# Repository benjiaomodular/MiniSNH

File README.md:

# MiniSNH

An analog sample-and-hold module for Eurorack. It has random gates and trigger outputs that are in-sync with trigger input.

Turning the bias knob to one side makes the probability of the gates firing on one side higher than the other.

# Versions

## v1.0 - Initial Prototype
Does not work!!

- No mounting holes
- Holes for jacks too small
- Swapped negative and postiive power pins of U5 and U6
- Gate in for comparator was wired the wrong way (always high)

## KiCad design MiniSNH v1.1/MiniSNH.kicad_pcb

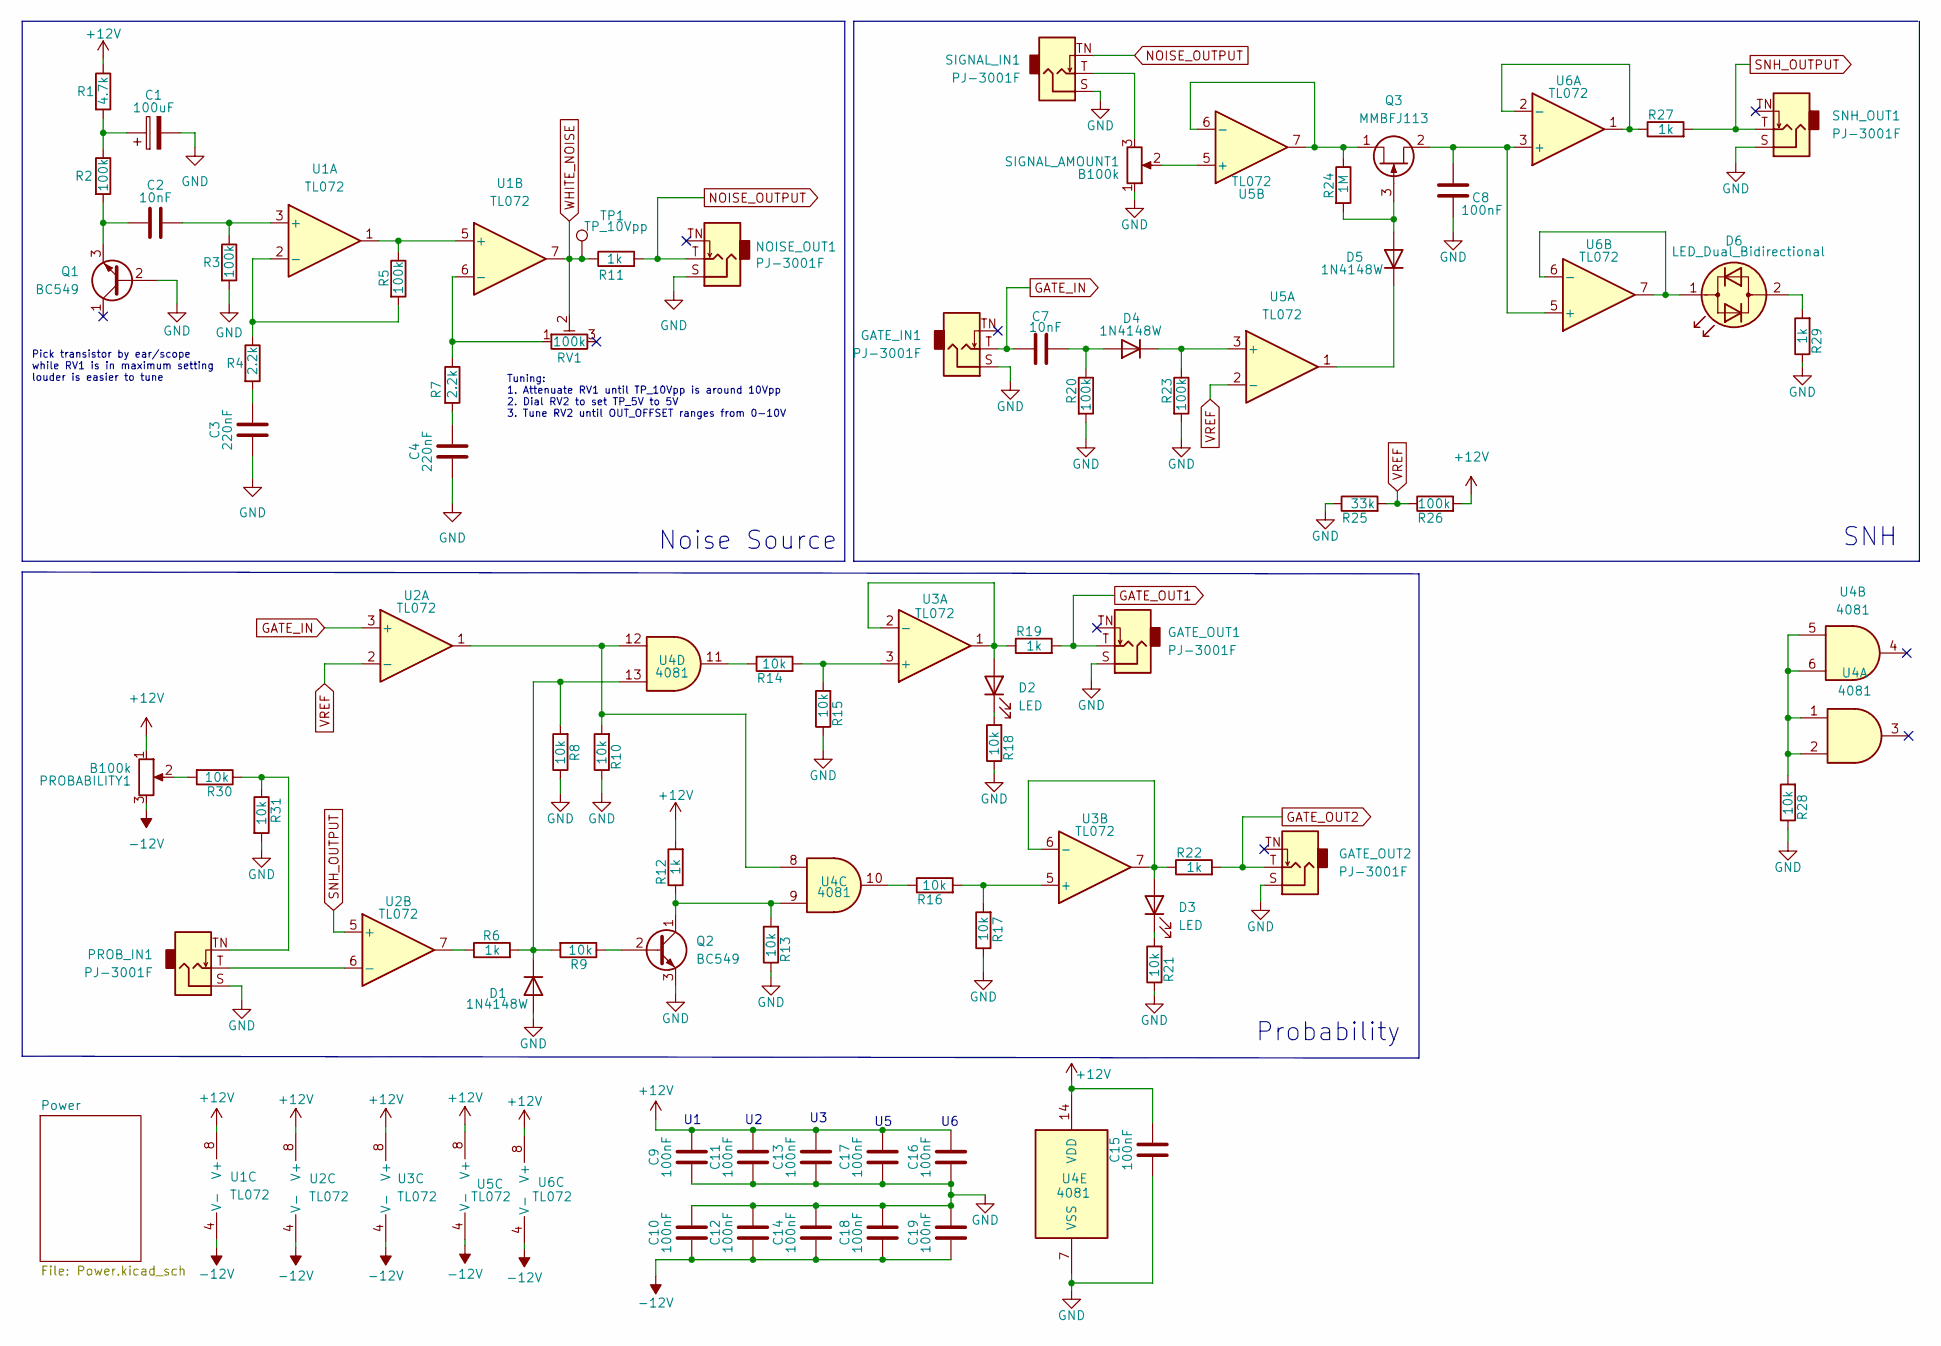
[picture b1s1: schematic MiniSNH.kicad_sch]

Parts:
C1: 100uF; Capacitor_Radial_D5.0mm_P2.5mm; Manufacturers Part Numb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 ESH107M010AC3AA
C2, C7: 10nF; C_0603_1608Metric_Pad1.08x0.95mm_HandSolder; Manufacturers Part Numb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 CC0603JRX7R9BB103
C3, C4: 220nF; C_0603_1608Metric_Pad1.08x0.95mm_HandSolder; Manufacturers Part Numb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 GCM188R71H224KA64D
C8, C9, C10, C11, C12, C13, C14, C15, C16, C17, C18, C19: 100nF; C_0603_1608Metric_Pad1.08x0.95mm_HandSolder; Manufacturers Part Numb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 CC0603JRX7R9BB104
D1, D4, D5: 1N4148W; D_SOD-123; Manufacturers Part Numb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 1N4148WQ-7-F
D2, D3: LED; LED_D3.0mm; Manufacturers Part Numb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 A-261
D6: LED_Dual_Bidirectional; LED_D3.0mm; Manufacturers Part Numb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 3ARG4HWC
GATE_IN1: PJ-3001F; AudioJack_3.5mm; Manufacturers Part Numb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 PJ-3001F
GATE_OUT1, GATE_OUT2: PJ-3001F; AudioJack_3.5mm; Manufacturers Part Numb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 PJ-3001F
NOISE_OUT1: PJ-3001F; AudioJack_3.5mm; Manufacturers Part Numb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 PJ-3001F
PROBABILITY1: B100k; Potentiometer_RV09_NoBracket; Manufacturers Part Numb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 RD901F-40-15R1-B100K
PROB_IN1: PJ-3001F; AudioJack_3.5mm; Manufacturers Part Numb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 PJ-3001F
Q1: BC549; TO-92_Inline_Wide; Manufacturers Part Numb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 BC548BTA
Q2: BC549; TO-92_Inline_Wide; Manufacturers Part Numb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 BC549BTF
Q3: MMBFJ113; SOT-23; Manufacturers Part Numb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 MMBFJ113
R1: 4.7k; R_0603_1608Metric_Pad0.98x0.95mm_HandSolder; Manufacturers Part Numb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 RC0603FR-074K7L
R2, R3, R5, R20, R23, R26: 100k; R_0603_1608Metric_Pad0.98x0.95mm_HandSolder; Manufacturers Part Numb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 RC0603FR-07100KL
R4, R7: 2.2k; R_0603_1608Metric_Pad0.98x0.95mm_HandSolder; Manufacturers Part Numb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 RK73B1JTTD222J
R6, R11, R12, R19, R22, R27, R29: 1k; R_0603_1608Metric_Pad0.98x0.95mm_HandSolder; Manufacturers Part Numb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 RC0603FR-071KL
R8, R9, R10, R13, R14, R15, R16, R17, R18, R21, R28, R30, R31: 10k; R_0603_1608Metric_Pad0.98x0.95mm_HandSolder; Manufacturers Part Numb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 AC0603FR-0710KL
R24: 1M; R_0603_1608Metric_Pad0.98x0.95mm_HandSolder; Manufacturers Part Numb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 RC0603FR-071ML
R25: 33k; R_0603_1608Metric_Pad0.98x0.95mm_HandSolder; Manufacturers Part Numb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 CR0603-FX-3302ELF
RV1: 100k; Potentiometer_Bourns_3266Y_Vertical; Manufacturers Part Numb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 PV36X104C01B00
SIGNAL_AMOUNT1: B100k; Potentiometer_RV09_NoBracket; Manufacturers Part Numb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 RD901F-40-15R1-B100K
SIGNAL_IN1: PJ-3001F; AudioJack_3.5mm; Manufacturers Part Numb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 PJ-3001F
SNH_OUT1: PJ-3001F; AudioJack_3.5mm; Manufacturers Part Numb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 PJ-3001F
TP1: TP_10Vpp; TestPoint_Pad_2.0x2.0mm
U1, U2, U3, U5, U6: TL072; SOIC-8_3.9x4.9mm_P1.27mm; Manufacturers Part Numb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 TL072CDT
U4: 4081; SOIC-14_3.9x8.7mm_P1.27mm; Manufacturers Part Numb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 CD4081BM96

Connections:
+12V: C9.2, C11.2, C13.2, C15.2, C16.2, C17.2, PROBABILITY1.1, R1.1, R12.2, R26.2, U1.8 (V+), U2.8 (V+), U3.8 (V+), U4.14 (VDD), U5.8 (V+), U6.8 (V+); also elsewhere on the board
-12V: C10.1, C12.1, C14.1, C18.1, C19.1, PROBABILITY1.3, U1.4 (V-), U2.4 (V-), U3.4 (V-), U5.4 (V-), U6.4 (V-); also elsewhere on the board
GATE_IN: C7.1, GATE_IN1.T, U2.3 (+)
GATE_OUT1: GATE_OUT1.T, R19.2
GATE_OUT2: GATE_OUT2.T, R22.2
GND: C1.2, C3.1, C4.1, C8.2, C9.1, C10.2, C11.1, C12.2, C13.1, C14.2, C15.1, C16.1, C17.1, C18.2, C19.2, D1.2 (A), GATE_IN1.S, GATE_OUT1.S, GATE_OUT2.S, NOISE_OUT1.S, PROB_IN1.S, Q1.2 (B), Q2.3 (E), R3.2, R8.1, R10.1, R13.1, R15.1, R17.1, R18.1, R20.2, R21.1, R23.2, R25.1, R28.1, R29.1, R31.2, SIGNAL_AMOUNT1.1, SIGNAL_IN1.S, SNH_OUT1.S, U4.7 (VSS); also elsewhere on the board
NOISE_OUTPUT: NOISE_OUT1.T, R11.2, SIGNAL_IN1.TN
unnamed: C1.1, R1.2, R2.1
unnamed: C2.1, Q1.3 (E), R2.2
unnamed: C2.2, R3.1, U1.3 (+)
unnamed: C3.2, R4.2
unnamed: C4.2, R7.2
unnamed: C7.2, D4.2 (A), R20.1
unnamed: C8.1, Q3.2 (S), U6.3 (+), U6.5 (+)
unnamed: D1.1 (K), R6.2, R8.2, R9.2, U4.13
unnamed: D2.1 (K), R18.2
unnamed: D2.2 (A), R19.1, U3.1, U3.2 (-)
unnamed: D3.1 (K), R21.2
unnamed: D3.2 (A), R22.1, U3.6 (-), U3.7
unnamed: D4.1 (K), R23.1, U5.3 (+)
unnamed: D5.1 (K), U5.1
unnamed: D5.2 (A), Q3.3 (G), R24.2
unnamed: D6.1 (KA), U6.6 (-), U6.7
unnamed: D6.2 (AK), R29.2
unnamed: PROBABILITY1.2, R30.2
unnamed: PROB_IN1.T, U2.6 (-)
unnamed: PROB_IN1.TN, R30.1, R31.1
unnamed: Q2.1 (C), R12.1, R13.2, U4.9
unnamed: Q2.2 (B), R9.1
unnamed: Q3.1 (D), R24.1, U5.6 (-), U5.7
unnamed: R4.1, R5.2, U1.2 (-)
unnamed: R5.1, U1.1, U1.5 (+)
unnamed: R6.1, U2.7
unnamed: R7.1, RV1.1, U1.6 (-)
unnamed: R10.2, U2.1, U4.8, U4.12
unnamed: R14.1, U4.11
unnamed: R14.2, R15.2, U3.3 (+)
unnamed: R16.1, U4.10
unnamed: R16.2, R17.2, U3.5 (+)
unnamed: R27.1, U6.1, U6.2 (-)
unnamed: R28.2, U4.1, U4.2, U4.5, U4.6
unnamed: SIGNAL_AMOUNT1.2, U5.5 (+)
unnamed: SIGNAL_AMOUNT1.3, SIGNAL_IN1.T
SNH_OUTPUT: R27.2, SNH_OUT1.T, U2.5 (+)
VREF: R25.2, R26.1, U2.2 (-), U5.2 (-)
WHITE_NOISE: R11.1, RV1.2, TP1.1, U1.7

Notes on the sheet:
Pick transistor by ear/scope while RV1 is in maximum setting louder is easier to tune
Probability
Noise Source
Tuning: 1. Attenuate RV1 until TP_10Vpp is around 10Vpp 2. Dial RV2 to set TP_5V to 5V 3. Tune RV2 until OUT_OFFSET ranges from 0-10V
SNH

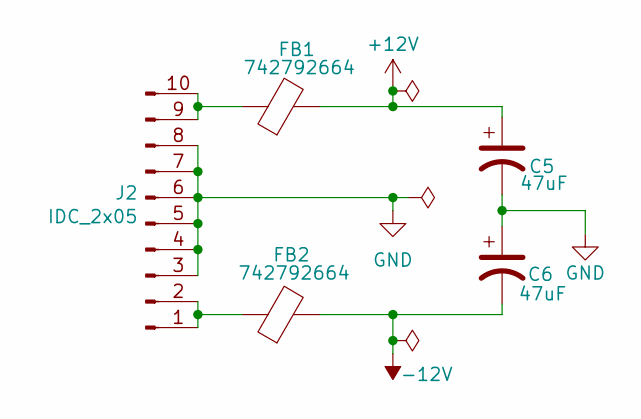
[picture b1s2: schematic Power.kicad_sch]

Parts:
C5, C6: 47uF; C_0805_2012Metric_Pad1.18x1.45mm_HandSolder; Manufacturers Part Numb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 GRM219R60J476ME44D
FB1, FB2: 742792664; C_0603_1608Metric_Pad1.08x0.95mm_HandSolder; Manufacturers Part Numb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 742792664
J2: IDC_2x05; IDC-Header_2x05_P2.54mm_Vertical; Manufacturers Part Numb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 X9555WV-2X05-6TV01; LCSC Part # C706914

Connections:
+12V: C5.1, FB1.2; also elsewhere on the board
-12V: C6.2, FB2.2; also elsewhere on the board
GND: C5.2, C6.1, J2.3, J2.4, J2.5, J2.6, J2.7, J2.8; also elsewhere on the board
unnamed: FB1.1, J2.9, J2.10
unnamed: FB2.1, J2.1, J2.2

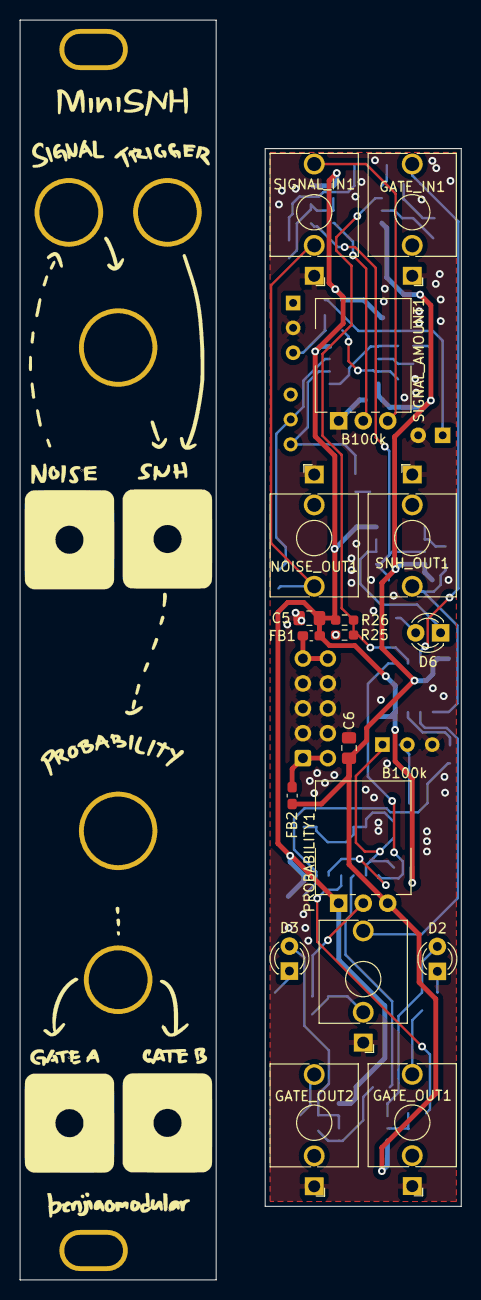
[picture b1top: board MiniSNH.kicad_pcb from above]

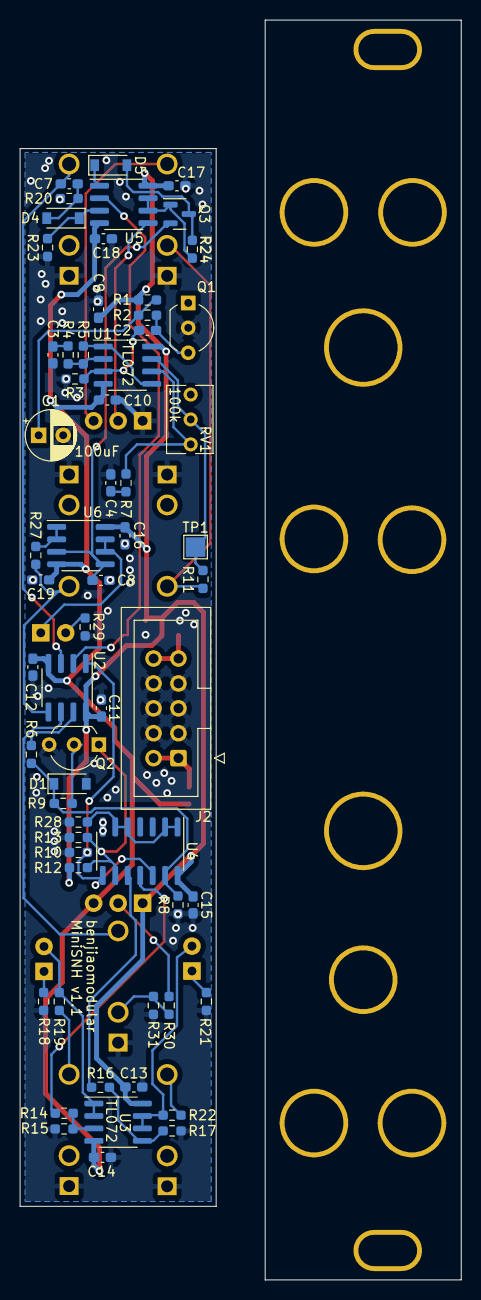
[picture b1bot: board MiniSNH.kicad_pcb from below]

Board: 2 copper layers, 20.0 x 107.9 mm, 79 parts (61 on the bottom side), 48 nets.

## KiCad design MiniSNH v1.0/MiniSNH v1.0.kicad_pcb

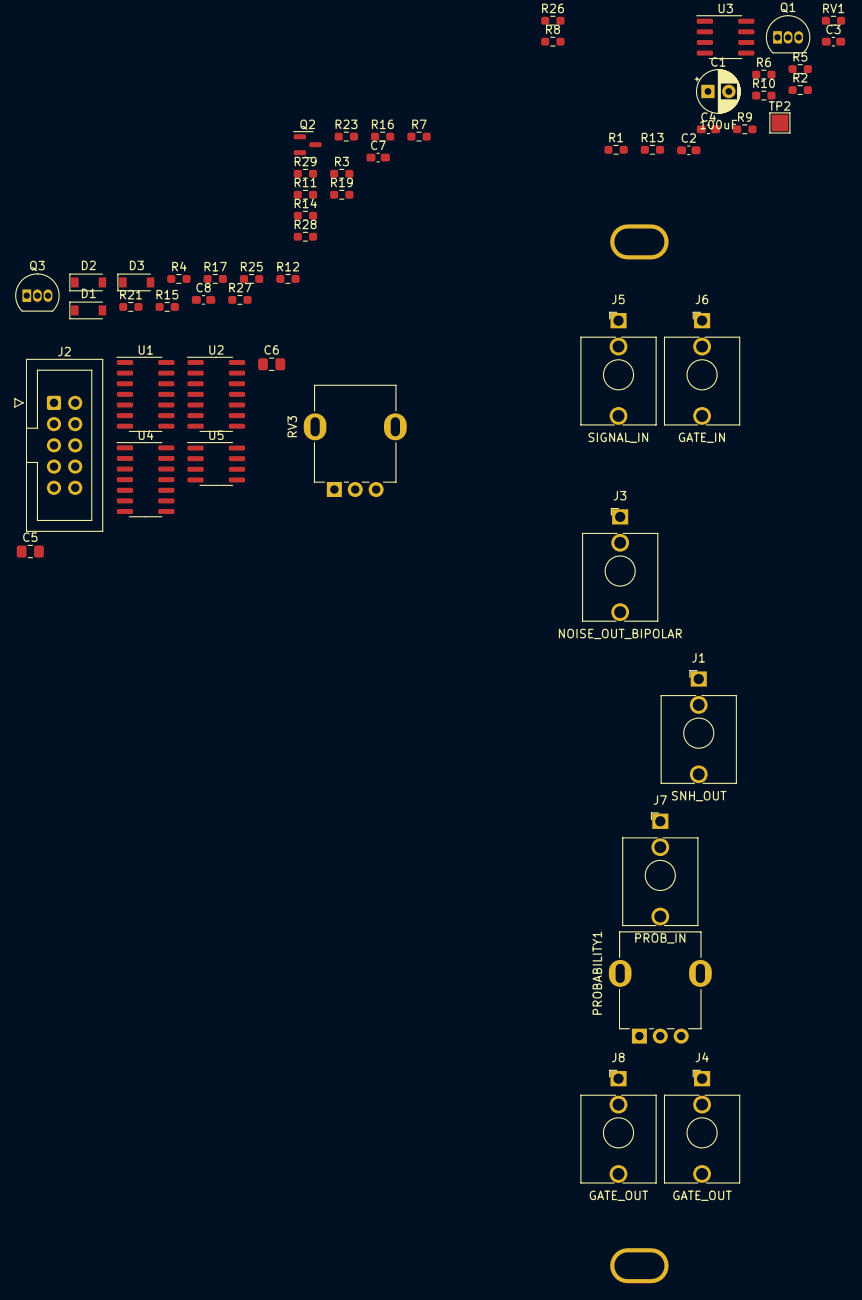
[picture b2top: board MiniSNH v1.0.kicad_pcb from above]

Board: 2 copper layers, 56 parts (0 on the bottom side), 41 nets, no tracks yet.

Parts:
C1: 100uF; Capacitor_Radial_D5.0mm_P2.5mm
C2, C7: 10nF; C_0603_1608Metric_Pad1.08x0.95mm_HandSolder
C3, C4: 220nF; C_0603_1608Metric_Pad1.08x0.95mm_HandSolder
C5, C6: 22uF; C_0805_2012Metric_Pad1.18x1.45mm_HandSolder
C8: 100nF; C_0603_1608Metric_Pad1.08x0.95mm_HandSolder
D1, D2, D3: 1N4148W; D_SOD-123
J1: SNH_OUT; AudioJack_3.5mm
J2: IDC_2x05; IDC-Header_2x05_P2.54mm_Vertical
J3: NOISE_OUT_BIPOLAR; AudioJack_3.5mm
J4, J8: GATE_OUT; AudioJack_3.5mm
J5: SIGNAL_IN; AudioJack_3.5mm
J6: GATE_IN; AudioJack_3.5mm
J7: PROB_IN; AudioJack_3.5mm
PROBABILITY1: B100k; Potentiometer_RV09
Q1: BC548; TO-92_Inline
Q2: MMBFJ113; SOT-23
Q3: BC549; TO-92_Inline
R1: 4.7k; R_0603_1608Metric_Pad0.98x0.95mm_HandSolder
R2, R5, R8, R9: 100k; R_0603_1608Metric_Pad0.98x0.95mm_HandSolder
R3, R7, R12, R16, R17, R21, R25, R26, R27, R28: 10k; R_0603_1608Metric_Pad0.98x0.95mm_HandSolder
R4: 33k; R_0603_1608Metric_Pad0.98x0.95mm_HandSolder
R6, R10: 2.2k; R_0603_1608Metric_Pad0.98x0.95mm_HandSolder
R11, R13, R15, R19, R23, R29: 1k; R_0603_1608Metric_Pad0.98x0.95mm_HandSolder
R14: 1M; R_0603_1608Metric_Pad0.98x0.95mm_HandSolder
RV1: 100k; R_0603_1608Metric_Pad0.98x0.95mm_HandSolder
RV3: B100k; Potentiometer_RV09
TP2: TP_10Vpp; TestPoint_Pad_2.0x2.0mm
U1, U2: TL074; SOIC-14_3.9x8.7mm_P1.27mm
U3, U5: TL072; SOIC-8_3.9x4.9mm_P1.27mm
U4: 4081; SOIC-14_3.9x8.7mm_P1.27mm

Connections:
+12V: C5.1, J2.9, J2.10, PROBABILITY1.1, R1.1, R8.2, R23.2, U1.4 (V+), U2.4 (V+), U3.8 (V+)
-12V: C6.2, J2.1, J2.2, PROBABILITY1.3, U1.11 (V-), U2.11 (V-), U3.4 (V-), U5.4 (V-)
GATE_IN: J6.TN, U1.5 (+)
GND: C1.2, C3.1, C4.1, C5.2, C6.1, C8.2, D3.2 (A), J1.S, J2.3, J2.4, J2.5, J2.6, J2.7, J2.8, J3.S, J4.S, J5.S, J6.S, J7.S, J8.S, Q1.2 (B), Q3.3 (E), R3.2, R4.1, R5.2, R7.2, R12.1, R16.1, R17.1, R26.1, R28.1, RV3.1, U4.7 (VSS)
NOISE_OUTPUT: J3.T, J5.TN, R13.2
unnamed: C1.1, R1.2, R2.1
unnamed: C2.1, Q1.3 (E), R2.2
unnamed: C2.2, R5.1, U3.3 (+)
unnamed: C3.2, R6.2
unnamed: C4.2, R10.2
unnamed: C7.1, J6.T
unnamed: C7.2, D2.2 (A), R3.1
unnamed: C8.1, Q2.2 (S), U2.10 (+)
unnamed: D1.1 (K), U2.1
unnamed: D1.2 (A), Q2.3 (G), R14.2
unnamed: D2.1 (K), R7.1, U2.3 (+)
unnamed: D3.1 (K), R15.2, R21.2, U4.2
unnamed: J4.T, R19.2
unnamed: J5.T, RV3.3
unnamed: J7.T, U1.2 (-)
unnamed: J7.TN, PROBABILITY1.2
unnamed: J8.T, R29.2
unnamed: Q2.1 (D), R14.1, U2.13 (-), U2.14
unnamed: Q3.1 (C), R17.2, R23.1, U4.6
unnamed: Q3.2 (B), R21.1
unnamed: R6.1, R9.2, U3.2 (-)
unnamed: R9.1, U3.1, U3.5 (+)
unnamed: R10.1, RV1.1, U3.6 (-)
unnamed: R11.1, U2.8, U2.9 (-)
unnamed: R12.2, R16.2, U1.7, U4.1, U4.5
unnamed: R15.1, U1.1
unnamed: R19.1, U1.8, U1.9 (-)
unnamed: R25.1, U4.3
unnamed: R25.2, R26.2, U1.10 (+)
unnamed: R27.1, U4.4
unnamed: R27.2, R28.2, U1.12 (+)
unnamed: R29.1, U1.13 (-), U1.14
unnamed: RV3.2, U2.12 (+)
SNH_OUTPUT: J1.T, R11.2, U1.3 (+)
VREF: R4.2, R8.1, U1.6 (-), U2.2 (-)
WHITE_NOISE: R13.1, RV1.2, TP2.1, U3.7

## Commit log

2023-05-20 initial push
2023-07-17 Added v1.1
2023-08-12 Added gerber files for v1.1
2023-08-12 Renamed broken gerber files
2023-08-14 Updated bom with corrections in parts numbers
2023-08-14 Added footprints for 100k trimmer and 33k
2023-11-04 Troubleshooting v1.1
